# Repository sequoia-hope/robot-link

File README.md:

# robot-link (comms)

### ▶ [Project page: schematic, PCB and 3D viewer](https://sequoia-hope.github.io/robot-link/)

A dev board for ST's 60 GHz contactless link: an **RP2350A** beside an
**ST60A3H1** (antenna in the package), 28 × 63 mm, six layers. Two boards
face each other a few centimetres apart and tunnel UART, GPIO, I²C or
USB 2.0 between them. The same board is either end. On the back there is a
connector for an **OV2640** camera module.

**Status: rev B captured, placed and routed. 100 parts, 83 nets; KiCad's DRC
and ERC report nothing, KiCad's own netlist of the drawn schematic matches
`tools/circuit.py` net for net, every placed part has an LCSC number and
the assembly check passes. Not fabricated, and no firmware yet.**

- **Rev A** (tag `rev-a`): the link board, four layers. Reviewed on
  2026-10-02; what the review found and changed is [below](#review).
- **Rev B**: rev A plus the [camera](#the-camera-rev-b), and six layers.

- `index.html` — status page with the board viewer (SCH, PCB, 3D); published
  from `main` at <https://sequoia-hope.github.io/robot-link/> by GitHub Pages, and
  served locally with `proj up comms`, address from `proj url comms`
- `hardware/comms/` — the KiCad project
- `tools/` — everything is generated; see below

## Why the ST60A3H1 and not the ST60A2G0

The board was asked for with the ST60A2G0. That part's ball map, pin
functions and the 60 GHz antenna and PCB-transition design are only in ST's
NDA package; the public data brief has the package outline and a block
diagram. The ST60A3H1 is the same family with a public data sheet
(DS14598) and the antenna in the package, so there is no 60 GHz copper to
design. It gives up speed: 480 Mbit/s (eUSB2) against the A2's 6.25 Gbit/s
SLVS.

## What is on it

| | |
|---|---|
| MCU | RP2350A with its core regulator, crystal, flash and decoupling as Raspberry Pi's minimal design (RP-006440) has them — the copper round the chip is read out of that board file |
| Link | ST60A3H1 on a grounded island with a copper-free ring round it, 3.5 mm in from the board edge, as on ST's X-NUCLEO-60K1A1 (B2379A) |
| Translator | TXS0108E, 1.8 V ↔ 3.3 V, on the configuration bus, the four tunnel pins, MODE_INT and LINK_STATUS; off until the RP2350 enables it. 4k7 pull-ups on the 1.8 V side of the configuration bus and of the tunnelled SCL/SDA |
| USB | PTN3222 eUSB2 repeater and two TS3USB221A switches: connector, RP2350 and the 60 GHz link, any two joined |
| Power | USB-C 5 V → AMS1117-3.3 → TLV75518P (1.8 V, off until GPIO11 goes high; dropping it is the ST60's power-on reset) |
| I/O | two 1 × 16 headers 0.9 in apart, SWD on JST-SH, BOOTSEL, RUN, power / link / user LEDs |
| Camera | on the back: a 24-way flex connector for the common OV2640 module (the ESP32-CAM's), its 2.8 V and 1.3 V regulators, pull-ups. Its signals are header GPIO |
| Mechanical | four M2.5 holes mirrored about the antenna's axis: a second board turned over on standoffs puts the two antennas on one line. Three fiducials |

GPIO map (`tools/circuit.py` has the reasons): 0–7 right-hand header · 8/9 USB
path selects · 10 RF_EN · 11 1.8 V enable · 12/13 tunnelled SDA/SCL (I2C0) ·
14 LINK_STATUS · 15 MODE_INT · 16/17 tunnelled TXD/RXD (UART0) · 18/19
configuration bus (I2C1; ST60A3H1 at 0x60, PTN3222 at 0x43) · 20 translator
enable · 21–24, 26–29 left-hand header · 25 LED.

## The camera (rev B)

For the bare OV2640 module with a 24-way, 0.5 mm flex tail: the one on the
ESP32-CAM. The connector (Hirose FH12-24S-0.5SH, bottom contact) is on the
**back** of the board. The tail goes in from the USB end with its contacts
toward the board; the module then lies on the back, behind the RP2350, with
its lens looking away from the board. That is the side away from the board
the 60 GHz link faces.

| Camera | GPIO | |
|---|---|---|
| Y2 – Y9 (data) | 0 – 7 | in order: one PIO `in pins, 8` |
| VSYNC | 21 | |
| SIOD / SIOC | 22 / 23 | I2C1, on its second pair of pins (the link's configuration bus is I2C1 on 18/19: move the peripheral, the buses do not share a wire). 4k7 pull-ups |
| PWDN | 24 | 10 k pull-up: the camera sleeps until this is driven low |
| HREF | 26 | |
| XCLK | 27 | from PWM slice 5 B, or PIO: 6 – 24 MHz, so 150 MHz ÷ 8, 10 or 12 (÷ 6 is 25 MHz, too fast). Low drive strength, slow slew: it runs beside PCLK |
| PCLK | 28 | |
| RESET | none | 10 k and 1 µF; the sensor has a software reset (COM7 bit 7), to be used once XCLK is running |

These are header pins, and with no camera plugged in they are nothing else:
26–28 are the ADC pins and have no resistor on them. 22, 23 and 24 keep
their pull-ups.

The sensor's core is on 1.3 V (OmniVision's data sheet from v1.8 on: 1.24 to
1.36 V. The older sheets, and the ESP32-CAM, say 1.2 V), its analogue side
on 2.8 V, its I/O on 3.3 V. The regulators have no enable: a fitted camera
in power-down draws 1 – 2 mA. To wake it: start XCLK, wait 10 ms, drive
PWDN low, reset it over SCCB, then configure.

The order of signals on GPIO 21–28 is not free. The camera's wiring is laid
by hand on the back, from the headers' own through-hole pads to the
connector, in one layer with nothing crossing, and only this order allows
that (`gen_board.camera_copper`).

**Checked, not tested:** which end of the connector is pin 1. The module
makers number the tail one way and the ESP32-CAM's schematic the other. The
board's pads were checked signal by signal, twice and independently, against
two module makers' mechanical drawings and Hirose's data sheet (contacts on
the face away from the lens; with the tail toward you and the contacts up,
NC and AGND on the right, Y0 and Y1 on the left). Check the module in hand
against that before plugging it in: a variant with a mirrored tail would be
the one way this is wrong.

An independent review of the camera addition (2026-10-02) confirmed the pin
order and found four things, all changed: the core supply (was 1.2 V), 100 nF
on each rail at the connector and wider supply tracks, more room round XCLK
where the wiring allows it, and the module's outline on the silkscreen, which
was 2.7 mm out. Left as they are: XCLK still runs 0.125 mm from PCLK and HREF
under the connector (the pads' order puts it between them); DOVDD is 3.3 V,
the data sheet's maximum, as on the ESP32-CAM.

With the headers soldered pins-down straight into a carrier board there is
about 2.5 mm under the board, and the module is 5.5 mm tall: it needs
sockets, or the headers the other way up.

## Board rules

Six layers, JLCPCB's JLC06161H-7628 stack: F.Cu parts and signals, In1 solid
ground, In2 and In3 routed signals, In4 supplies (+3V3, with +1V8 over the
link section), B.Cu signals, the camera's wiring and its parts. The outer
prepreg is the same 0.21 mm as JLCPCB's four-layer stack, so the antenna's
ground and the USB pairs sit as they did on rev A. Routed signals are
0.125 mm track and clearance (JLCPCB's floor is 0.09), and so are the ST60's
ball escapes. The USB pairs on the back are 0.28 mm wide and 0.16 mm apart.
Vias 0.46 / 0.2 mm, all through.

Why six: rev A routed on four. With the camera's wiring and parts on the
back, the same board on four layers left two to seven nets open in each of
three attempts, the nets at the RP2350's pins that had been marginal on
rev A. On six it closes in one or two.

## Ordering and using it

- **JLCPCB Standard PCBA, not Economic**: the ST60A3H1 is a 0.4 mm BGA, and
  Economic stops at 0.5 mm. Standard wants edge rails (JLCPCB adds them) and
  fiducials (three are on the board). Ask for a 0.10 mm stencil.
- Fifteen parts are on the back (the camera's): assembly is two-sided. To
  build the board without the camera, leave the back unassembled; nothing
  on the front depends on it.
- Green solder mask: the ST60's mask openings are 0.30 mm on 0.25 mm lands,
  which leaves 0.10 mm webs between balls, JLCPCB's minimum for green.
- Four vias sit in the gap in the ST60's ball field, tented. Plugged vias
  are the safer order.
- Fit the headers **pins down**, and use **nylon** standoffs at the antenna
  end (H1, H2): metal 11 mm from the patch is inside its beam.
- Firmware: +1V8 is off at reset. Raise GPIO11, wait 2.25 ms, then enable
  the translator (GPIO20) and RF_EN (GPIO10). Before dropping +1V8, take
  both low first. The PTN3222 is held in reset whenever the RF link is down,
  so anything written to it has to be written again after each link-up.
- VBUS on the headers is the USB-C connector's VBUS, direct: it is an
  output. Do not feed 5 V into it with a host plugged in.
- Pull-ups added on J2/J3 (the 3.3 V side of the translator) should be
  8k2 or more.

## The tools

```
python3 tools/circuit.py        # the netlist, as data, and its checks
python3 tools/symbols.py        # hardware/parts/comms.kicad_sym
python3 tools/footprints.py     # hardware/parts/comms.pretty
python3 tools/placement.py      # where every part sits, and its checks
python3 tools/gen_board.py --force   # project, schematic and the unrouted board (DISCARDS routing)
python3 tools/route.py          # freerouting on a stripped copy, results copied back, stitching
python3 tools/schdraw.py --check     # KiCad's netlist of the schematic against circuit.py
python3 tools/assembly.py       # IPC-2581, the pin-1 answers beside it, boardvis's check
python3 tools/regen.py          # every check, then the viewer and the status line on index.html
```

`gen_board.py` lays the copper that is decided rather than routed: Raspberry
Pi's tracks and pours round the RP2350, the ST60's ball field and antenna
ground (ST's own via pattern, hole for hole where it fits), the 480 Mbit/s
USB pair, a via beside every pad on a plane net,
the camera's wiring.
`route.py` hands the remaining ~70 signals to freerouting 2.2.4
(`~/Software/magnet/route`); it is not deterministic, so it makes several
attempts and keeps the first that closes everything.

## Review

Two independent passes on 2026-10-02, one over the schematic against the
data sheets and one over the layout against JLCPCB's limits and ST's
reference board. Neither found anything that would stop the board working.
What they found, and what was done:

| Finding | Done |
|---|---|
| The antenna ground was a quarter of ST's: 13 vias in the island and 15 round it, where B2379A has 53 and 56; the signals crossed the island on a diagonal | The ball field is laid as ST lays it: nine signals straight out through one side of the ring, the supply along the top of them. ST's vias are taken from its drill file: 33 fit in the island and 45 round it |
| +1V8 fall time marginal against the ST60's 1 ms limit (3.3 µF on a 120 Ω discharge) | 1.8 µF on the rail; the regulator's enable is pulled down, so the rail only rises with 3V3 settled |
| MODE_INT strap undefined if +1V8 is cycled with the translator on | 4k7 to ground on MODE_INT |
| No pull-ups on the I²C lines; ST60 and PTN3222 both want external ones | 4k7 to +1V8 on the configuration bus and on GPIO[2]/[3] |
| USB pair geometry computed at 100 Ω; it crossed two plane splits and ran 2.4 mm over no plane | 0.28 / 0.16 mm (89 Ω by the reviewer's field solver); +1V8 plane redrawn so the pair has +3V3 under it throughout; its copper now 0.8 mm from the board edge, not 0.57 |
| Solder-mask webs between balls 0.075 mm | Mask opening 0.30 mm, webs 0.10 mm |
| Silkscreen under JLCPCB's 1.0 mm / 0.15 mm | Back labels 1.0 mm, front 0.8 mm (what fits a 2.54 mm pitch), all lines 0.15 mm |
| VBUS ran under the USB-C shell | Joined on the back |
| LEDs near dark at 1 kΩ (Vf 3.1 V) | 220 Ω |
| No fiducials | Three |
| Four 3V3 capacitors at the RP2350 fed only through the ring under the chip; one via pair into the plane at the regulator | A via beside each of the four capacitors; five more at the regulator's tab |

Left as it is, knowingly:

- **TXS0108E on the I²C lines.** The reviewer would rather have a pass-FET
  translator with no edge accelerators there: the ST60 has no glitch filter
  on CFG_SCL. ST's own board uses an auto-direction part (ST2378E) on the
  same lines; that part's data sheet was not read. If the configuration bus
  misbehaves with wiring on J2, this is the first place to look.
- **AMS1117 with ceramic output capacitors**, as Raspberry Pi's reference has
  an 1117: outside what the AMS data sheet characterises (22 µF tantalum).
  It needs about 1 V of headroom, so VBUS has to stay above 4.35 V.
- **The crystal** is servodrive's 2520 (CL 20 pF) with 27 pF, where Raspberry
  Pi specifies an ABM8-272 with 15 pF and says any change needs testing.
- **USB pair skew**: D− is 1.1 mm longer than D+ between the connector and
  the first switch (its two pads are joined under the shell). The long run
  to the repeater is matched to 0.05 mm.
- **The ground guard round the crystal** in the reference was not copied;
  three signals pass within 0.13 mm of the crystal nets.

## Not yet verified

- Nothing has been built. The ST60A3H1 land and the PTN3222 land are drawn
  from the manufacturers' drawings, not from a part in hand.
- The antenna island copies ST's dimensions and vias off their Gerbers; the
  pattern on this board has not been simulated or measured, and it has
  fewer vias than ST's where this board's tracks are in the way.
- The 89 Ω figure for the USB pairs is one reviewer's solver, checked
  against a textbook formula only. Confirm with JLCPCB's calculator.
- JLCPCB capability figures were read off their site on 2026-10-02 through
  a summarising tool, not from the raw pages. Check them at order time.
- Several pin-1 answers in the assembly sidecar are package convention,
  not read off that part's data sheet; the sidecar says which.
- Rev B's camera connector: see "Checked, not tested" above. The camera's
  wiring runs 15 to 40 mm on the back over the supply plane; nothing about
  its signal integrity at a 20 MHz pixel clock has been measured.
- The 2.8 V regulator is listed as UMW's XC6206; its data sheet numbers the
  pins oddly, and the reviewer read it as the same physical order as Torex's.

## Next

Firmware: the link's bring-up sequence, a PIO capture for the camera. Then
a first build.

CERN-OHL-P.

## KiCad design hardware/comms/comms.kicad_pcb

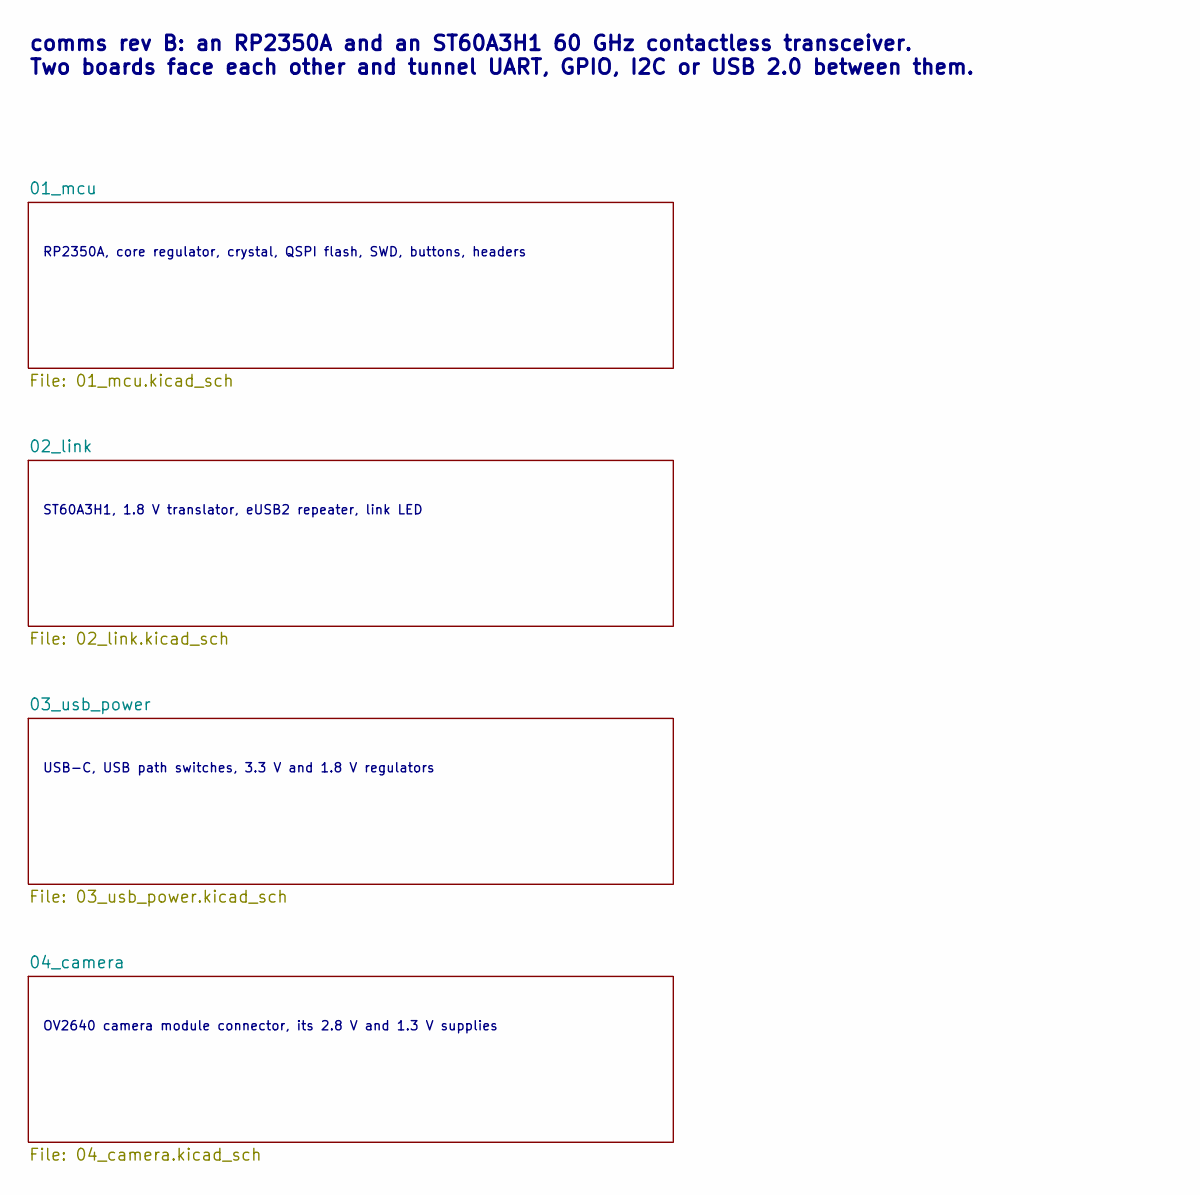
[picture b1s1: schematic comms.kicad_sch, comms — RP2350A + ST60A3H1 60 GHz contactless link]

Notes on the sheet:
RP2350A, core regulator, crystal, QSPI flash, SWD, buttons, headers
ST60A3H1, 1.8 V translator, eUSB2 repeater, link LED
USB-C, USB path switches, 3.3 V and 1.8 V regulators
OV2640 camera module connector, its 2.8 V and 1.3 V supplies
comms rev B: an RP2350A and an ST60A3H1 60 GHz contactless transceiver. Two boards face each other and tunnel UART, GPIO, I2C or USB 2.0 between them.

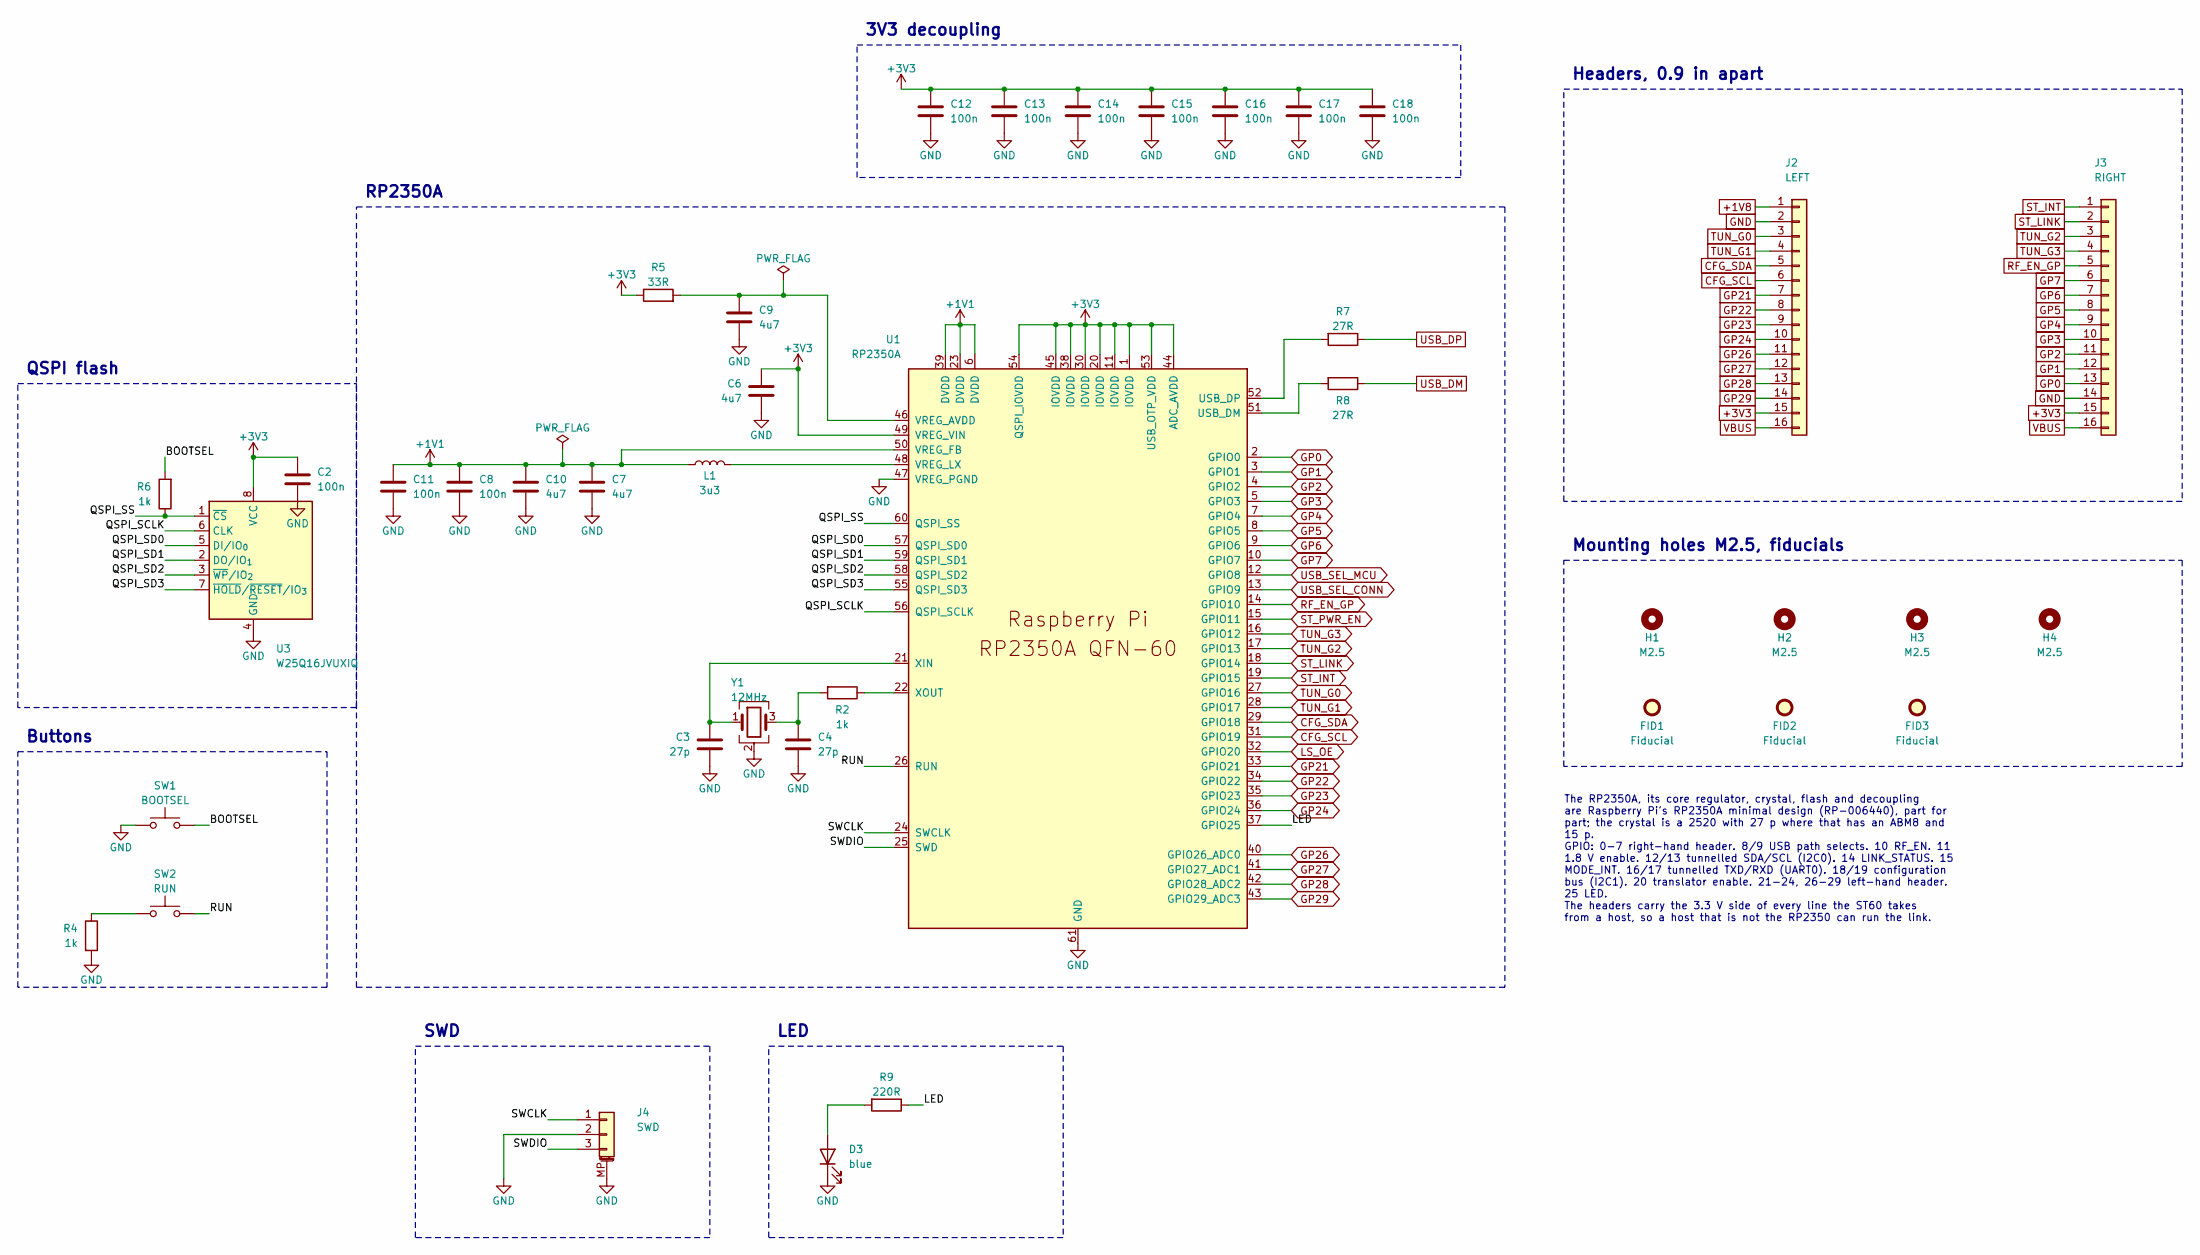
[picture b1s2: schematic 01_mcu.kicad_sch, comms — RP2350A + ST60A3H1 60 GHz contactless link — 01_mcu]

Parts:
C2, C8, C11, C12, C13, C14, C15, C16, C17, C18: 100n; C_0402_1005Metric
C3, C4: 27p; C_0402_1005Metric
C6, C7: 4u7; C_0402_1005Metric_small_pads
C9, C10: 4u7; C_0402_1005Metric
D3: blue; LED_0603_1608Metric
FID1, FID2, FID3: Fiducial; Fiducial_1mm_Mask2mm
H1, H2, H3, H4: M2.5; MountingHole_2.7mm_M2.5
J2: LEFT; PinHeader_1x16_P2.54mm_Vertical
J3: RIGHT; PinHeader_1x16_P2.54mm_Vertical
J4: SWD; JST_SH_SM03B-SRSS-TB_1x03-1MP_P1.00mm_Horizontal
L1: 3u3; L_pol_2016
R2, R4, R6: 1k; R_0402_1005Metric
R5: 33R; R_0402_1005Metric
R7, R8: 27R; R_0402_1005Metric
R9: 220R; R_0402_1005Metric
SW1: BOOTSEL; SW_SPST_B3U-1000P
SW2: RUN; SW_SPST_B3U-1000P
U1: RP2350A; RP2350-QFN-60-1EP_7x7_P0.4mm_EP3.4x3.4mm_ThermalVias
U3: W25Q16JVUXIQ; Winbond_USON-8-1EP_3x2mm_P0.5mm_EP0.2x1.6mm
Y1: 12MHz; Crystal_SMD_2520-4Pin_2.5x2.0mm

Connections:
+1V1: C7.1, C8.1, C10.1, C11.1, L1.1, U1.6 (DVDD), U1.23 (DVDD), U1.39 (DVDD), U1.50 (VREG_FB)
+1V8: J2.1; also elsewhere on the board
+3V3: C2.1, C6.1, C12.1, C13.1, C14.1, C15.1, C16.1, C17.1, C18.1, J2.15, J3.15, R5.1, U1.1 (IOVDD), U1.11 (IOVDD), U1.20 (IOVDD), U1.30 (IOVDD), U1.38 (IOVDD), U1.44 (ADC_AVDD), U1.45 (IOVDD), U1.49 (VREG_VIN), U1.53 (USB_OTP_VDD), U1.54 (QSPI_IOVDD), U3.8 (VCC); also elsewhere on the board
BOOTSEL: R6.2, SW1.2
CFG_SCL: J2.6, U1.31 (GPIO19); also elsewhere on the board
CFG_SDA: J2.5, U1.29 (GPIO18); also elsewhere on the board
GND: C2.2, C3.2, C4.2, C6.2, C7.2, C8.2, C9.2, C10.2, C11.2, C12.2, C13.2, C14.2, C15.2, C16.2, C17.2, C18.2, D3.1 (K), J2.2, J3.14, J4.2, J4.MP (MountPin), R4.2, SW1.1, U1.47 (VREG_PGND), U1.61 (GND), U3.4 (GND), Y1.2 (G), Y1.4 (G); also elsewhere on the board
GP0: J3.13, U1.2 (GPIO0); also elsewhere on the board
GP1: J3.12, U1.3 (GPIO1); also elsewhere on the board
GP2: J3.11, U1.4 (GPIO2); also elsewhere on the board
GP3: J3.10, U1.5 (GPIO3); also elsewhere on the board
GP4: J3.9, U1.7 (GPIO4); also elsewhere on the board
GP5: J3.8, U1.8 (GPIO5); also elsewhere on the board
GP6: J3.7, U1.9 (GPIO6); also elsewhere on the board
GP7: J3.6, U1.10 (GPIO7); also elsewhere on the board
GP21: J2.7, U1.33 (GPIO21); also elsewhere on the board
GP22: J2.8, U1.34 (GPIO22); also elsewhere on the board
GP23: J2.9, U1.35 (GPIO23); also elsewhere on the board
GP24: J2.10, U1.36 (GPIO24); also elsewhere on the board
GP26: J2.11, U1.40 (GPIO26_ADC0); also elsewhere on the board
GP27: J2.12, U1.41 (GPIO27_ADC1); also elsewhere on the board
GP28: J2.13, U1.42 (GPIO28_ADC2); also elsewhere on the board
GP29: J2.14, U1.43 (GPIO29_ADC3)
LED: R9.1, U1.37 (GPIO25)
LED_A: D3.2 (A), R9.2
LS_OE: U1.32 (GPIO20); also elsewhere on the board
QSPI_SCLK: U1.56 (QSPI_SCLK), U3.6 (CLK)
QSPI_SD0: U1.57 (QSPI_SD0), U3.5 (DI/IO_{0})
QSPI_SD1: U1.59 (QSPI_SD1), U3.2 (DO/IO_{1})
QSPI_SD2: U1.58 (QSPI_SD2), U3.3 (~WP/IO_{2})
QSPI_SD3: U1.55 (QSPI_SD3), U3.7 (~HOLD/~RESET/IO_{3})
QSPI_SS: R6.1, U1.60 (QSPI_SS), U3.1 (~CS)
RF_EN_GP: J3.5, U1.14 (GPIO10); also elsewhere on the board
RUN: SW2.2, U1.26 (RUN)
RUN_SW: R4.1, SW2.1
ST_INT: J3.1, U1.19 (GPIO15); also elsewhere on the board
ST_LINK: J3.2, U1.18 (GPIO14); also elsewhere on the board
ST_PWR_EN: U1.15 (GPIO11); also elsewhere on the board
SWCLK: J4.1, U1.24 (SWCLK)
SWDIO: J4.3, U1.25 (SWD)
TUN_G0: J2.3, U1.27 (GPIO16); also elsewhere on the board
TUN_G1: J2.4, U1.28 (GPIO17); also elsewhere on the board
TUN_G2: J3.3, U1.17 (GPIO13); also elsewhere on the board
TUN_G3: J3.4, U1.16 (GPIO12); also elsewhere on the board
USB_DM: R8.1; also elsewhere on the board
USB_DM_C: R8.2, U1.51 (USB_DM)
USB_DP: R7.1; also elsewhere on the board
USB_DP_C: R7.2, U1.52 (USB_DP)
USB_SEL_CONN: U1.13 (GPIO9); also elsewhere on the board
USB_SEL_MCU: U1.12 (GPIO8); also elsewhere on the board
VBUS: J2.16, J3.16; also elsewhere on the board
VREG_AVDD: C9.1, R5.2, U1.46 (VREG_AVDD)
VREG_LX: L1.2, U1.48 (VREG_LX)
XIN: C3.1, U1.21 (XIN), Y1.1
XOUT: R2.1, U1.22 (XOUT)
XTAL2: C4.1, R2.2, Y1.3

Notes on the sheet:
RP2350A
3V3 decoupling
QSPI flash
Buttons
SWD
LED
Headers, 0.9 in apart
Mounting holes M2.5, fiducials
The RP2350A, its core regulator, crystal, flash and decoupling are Raspberry Pi's RP2350A minimal design (RP-006440), part for part; the crystal is a 2520 with 27 p where that has an ABM8 and 15 p. GPIO: 0-7 right-hand header. 8/9 USB path selects. 10 RF_EN. 11 1.8 V enable. 12/13 tunnelled SDA/SCL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

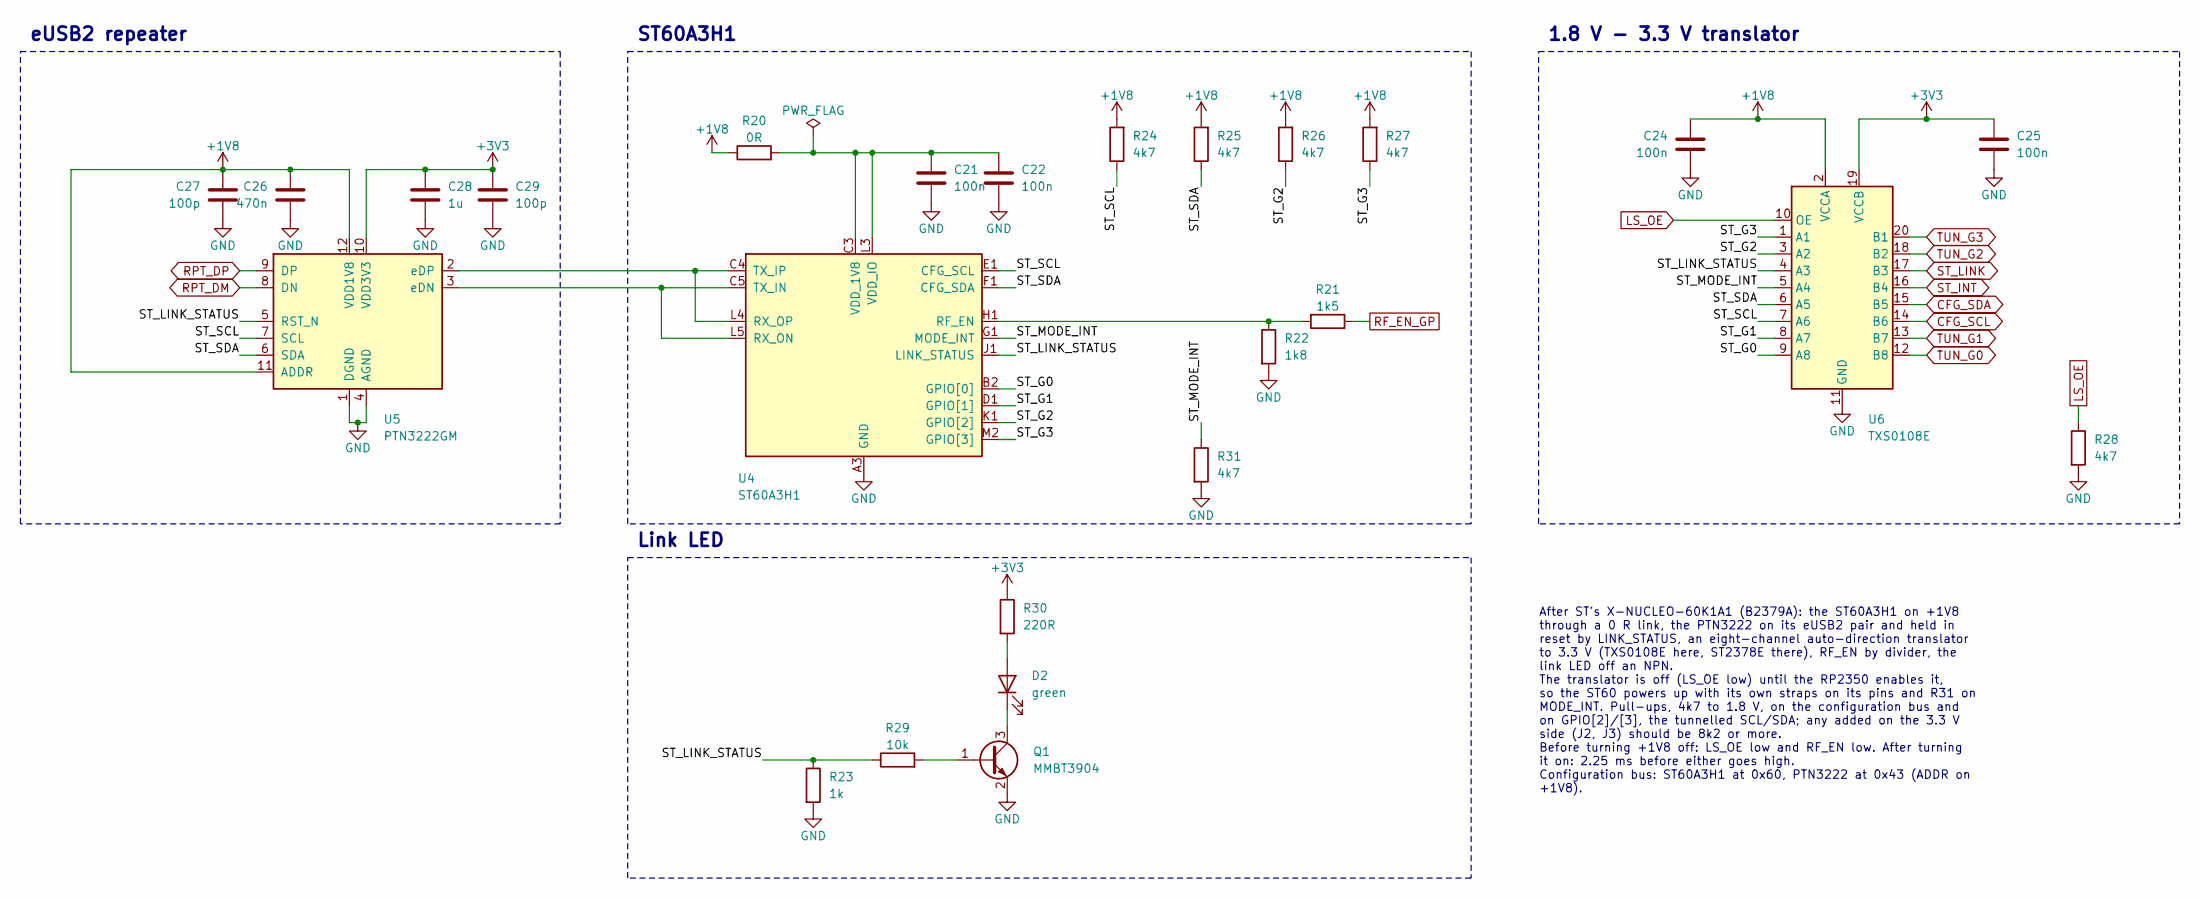
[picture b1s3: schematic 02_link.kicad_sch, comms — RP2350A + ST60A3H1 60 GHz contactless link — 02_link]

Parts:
C21, C22, C24, C25: 100n; C_0402_1005Metric
C26: 470n; C_0402_1005Metric
C27, C29: 100p; C_0402_1005Metric
C28: 1u; C_0402_1005Metric
D2: green; LED_0603_1608Metric
Q1: MMBT3904; SOT-23
R20: 0R; R_0402_1005Metric
R21: 1k5; R_0402_1005Metric
R22: 1k8; R_0402_1005Metric
R23: 1k; R_0402_1005Metric
R24, R25, R26, R27, R28, R31: 4k7; R_0402_1005Metric
R29: 10k; R_0402_1005Metric
R30: 220R; R_0402_1005Metric
U4: ST60A3H1; ST_VFBGA-23_AiP_2.95x4.07mm_P0.4mm
U5: PTN3222GM; NXP_XQFN-12_1.75x2.2mm_P0.4mm
U6: TXS0108E; TSSOP-20_4.4x6.5mm_P0.65mm

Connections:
+1V8: C24.1, C26.1, C27.1, R20.1, R24.2, R25.2, R26.2, R27.2, U5.11 (ADDR), U5.12 (VDD1V8), U6.2 (VCCA); also elsewhere on the board
+3V3: C25.1, C28.1, C29.1, R30.1, U5.10 (VDD3V3), U6.19 (VCCB); also elsewhere on the board
CFG_SCL: U6.14 (B6); also elsewhere on the board
CFG_SDA: U6.15 (B5); also elsewhere on the board
EUSB_N: U4.C5 (TX_IN), U4.L5 (RX_ON), U5.3 (eDN)
EUSB_P: U4.C4 (TX_IP), U4.L4 (RX_OP), U5.2 (eDP)
GND: C21.2, C22.2, C24.2, C25.2, C26.2, C27.2, C28.2, C29.2, Q1.2 (E), R22.2, R23.2, R28.2, R31.2, U4.A3 (GND), U4.A4 (GND), U4.A5 (GND), U4.C6 (GND), U4.L6 (GND), U4.N3 (GND), U4.N4 (GND), U4.N5 (GND), U5.1 (DGND), U5.4 (AGND), U6.11 (GND); also elsewhere on the board
LINK_A: D2.2 (A), R30.2
LINK_B: Q1.1 (B), R29.2
LINK_K: D2.1 (K), Q1.3 (C)
LS_OE: R28.1, U6.10 (OE); also elsewhere on the board
RF_EN_GP: R21.1; also elsewhere on the board
RPT_DM: U5.8 (DN); also elsewhere on the board
RPT_DP: U5.9 (DP); also elsewhere on the board
ST_G0: U4.B2 (GPIO[0]), U6.9 (A8)
ST_G1: U4.D1 (GPIO[1]), U6.8 (A7)
ST_G2: R26.1, U4.K1 (GPIO[2]), U6.3 (A2)
ST_G3: R27.1, U4.M2 (GPIO[3]), U6.1 (A1)
ST_INT: U6.16 (B4); also elsewhere on the board
ST_LINK: U6.17 (B3); also elsewhere on the board
ST_LINK_STATUS: R23.1, R29.1, U4.J1 (LINK_STATUS), U5.5 (RST_N), U6.4 (A3)
ST_MODE_INT: R31.1, U4.G1 (MODE_INT), U6.5 (A4)
ST_RF_EN: R21.2, R22.1, U4.H1 (RF_EN)
ST_SCL: R24.1, U4.E1 (CFG_SCL), U5.7 (SCL), U6.7 (A6)
ST_SDA: R25.1, U4.F1 (CFG_SDA), U5.6 (SDA), U6.6 (A5)
ST_VDD: C21.1, C22.1, R20.2, U4.C3 (VDD_1V8), U4.L3 (VDD_IO)
TUN_G0: U6.12 (B8); also elsewhere on the board
TUN_G1: U6.13 (B7); also elsewhere on the board
TUN_G2: U6.18 (B2); also elsewhere on the board
TUN_G3: U6.20 (B1); also elsewhere on the board

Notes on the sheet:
eUSB2 repeater
ST60A3H1
1.8 V - 3.3 V translator
Link LED
After ST's X-NUCLEO-60K1A1 (B2379A): the ST60A3H1 on +1V8 through a 0 R link, the PTN3222 on its eUSB2 pair and held in reset by LINK_STATUS, an eight-channel auto-direction translator to 3.3 V (TXS0108E here, ST2378E there), RF_EN by divider, the link LED off an NPN. The translator is off (LS_OE l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

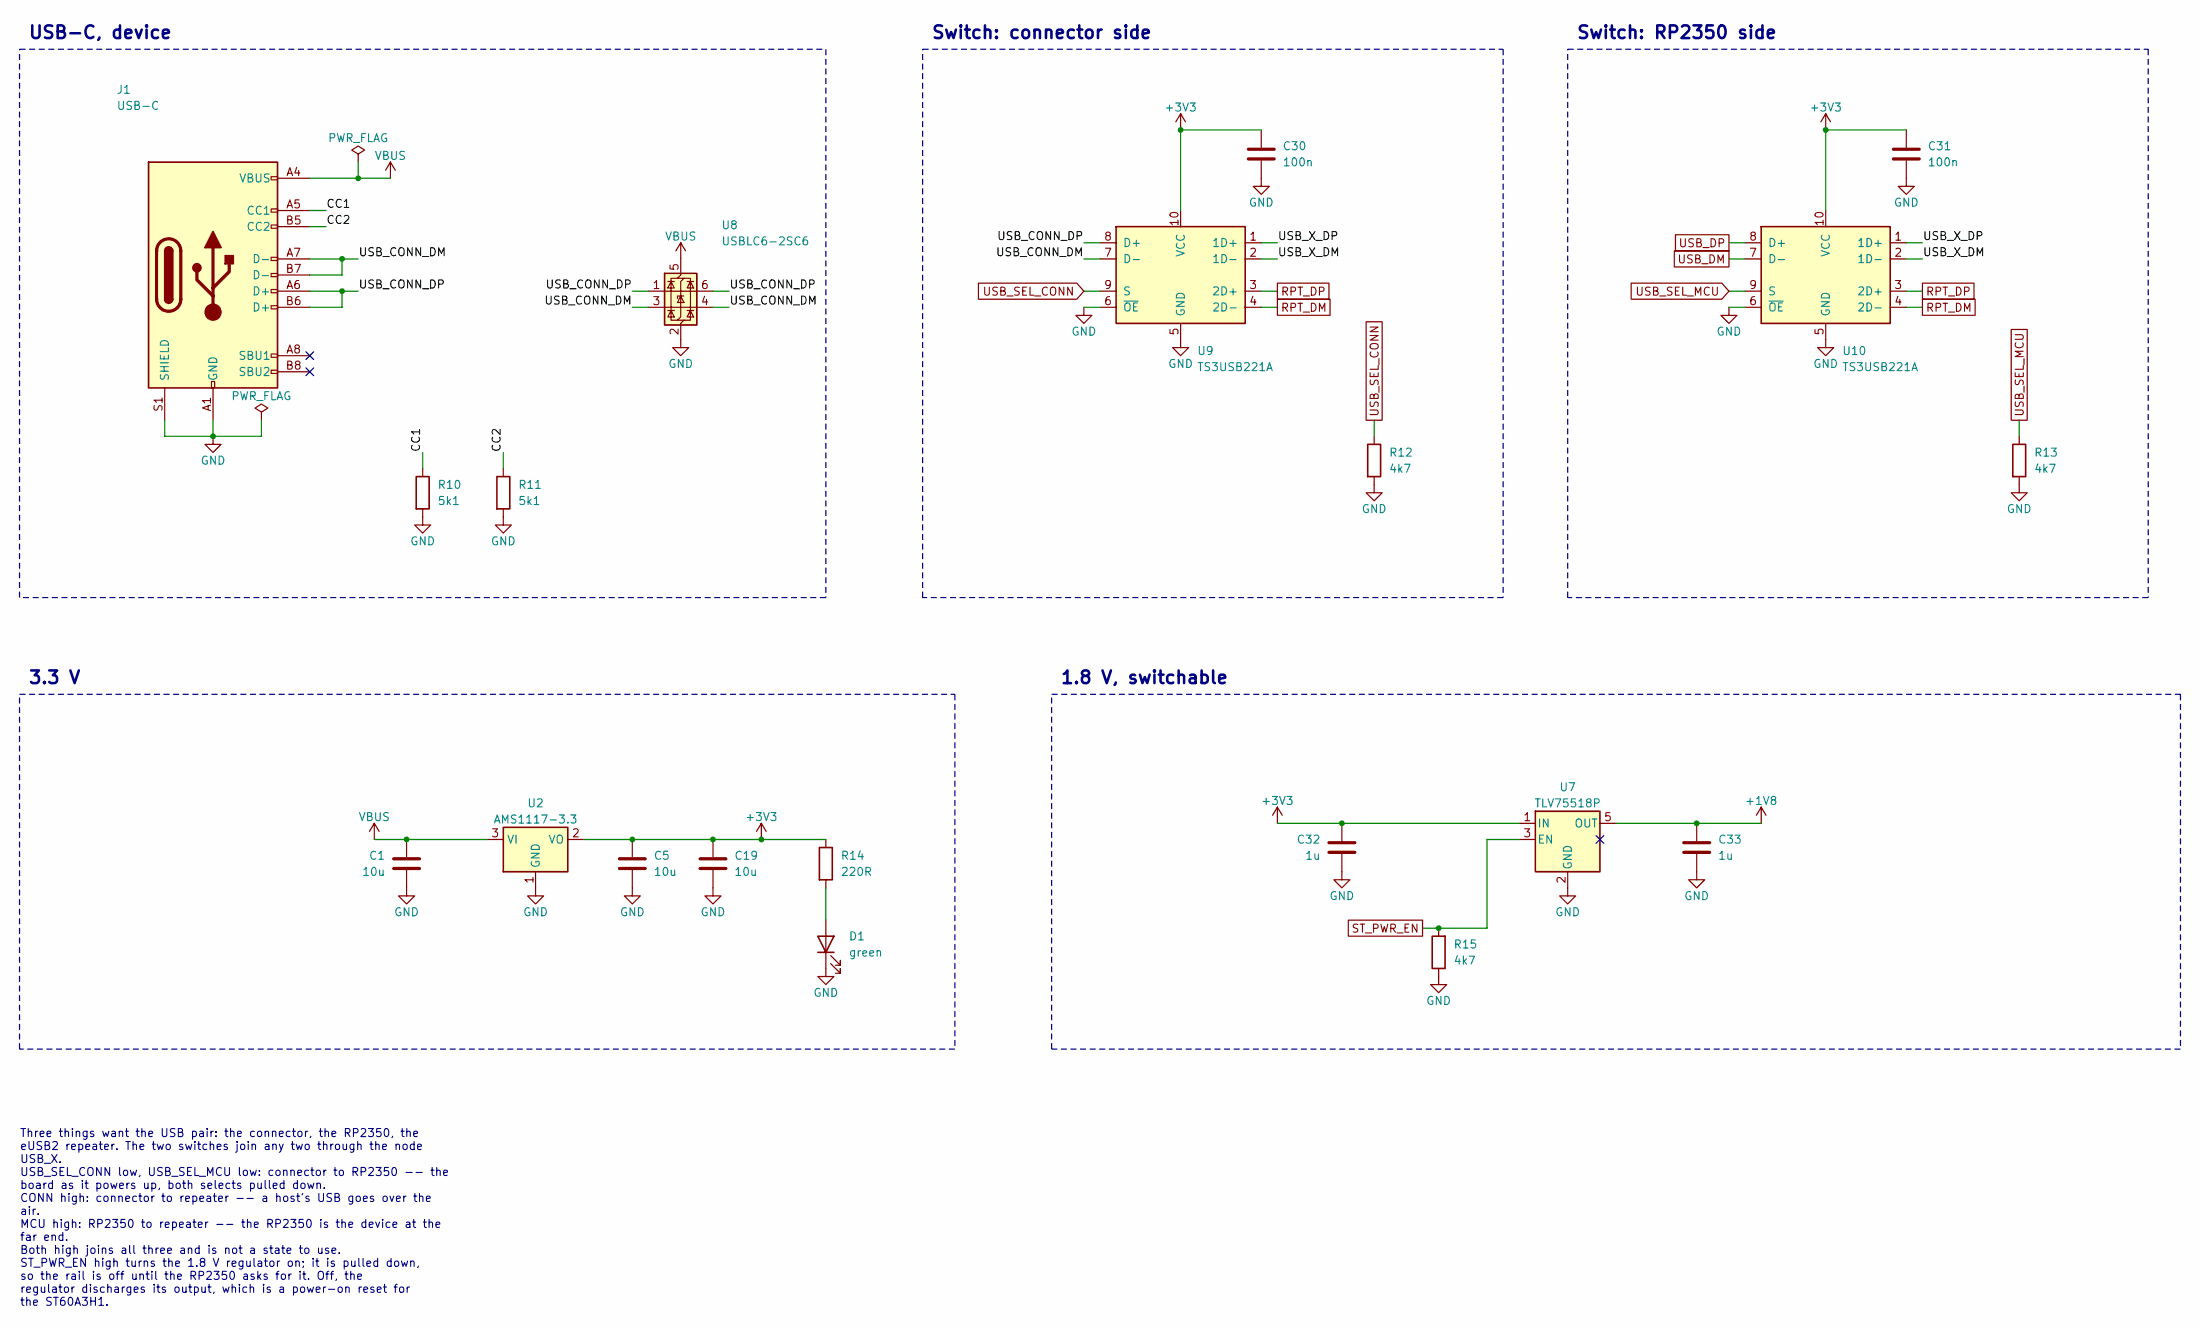
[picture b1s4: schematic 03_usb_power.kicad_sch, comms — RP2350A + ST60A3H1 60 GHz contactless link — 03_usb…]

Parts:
C1, C5, C19: 10u; C_0805_2012Metric
C30, C31: 100n; C_0402_1005Metric
C32, C33: 1u; C_0402_1005Metric
D1: green; LED_0603_1608Metric
J1: USB-C; USB_C_Receptacle_HRO_TYPE-C-31-M-12
R10, R11: 5k1; R_0402_1005Metric
R12, R13, R15: 4k7; R_0402_1005Metric
R14: 220R; R_0402_1005Metric
U2: AMS1117-3.3; SOT-223-3_TabPin2
U7: TLV75518P; SOT-23-5
U8: USBLC6-2SC6; SOT-23-6
U9, U10: TS3USB221A; Texas_UQFN-10_1.5x2mm_P0.5mm

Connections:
+1V8: C33.1, U7.5 (OUT); also elsewhere on the board
+3V3: C5.1, C19.1, C30.1, C31.1, C32.1, R14.1, U2.2 (VO), U7.1 (IN), U9.10 (VCC), U10.10 (VCC); also elsewhere on the board
CC1: J1.A5 (CC1), R10.1
CC2: J1.B5 (CC2), R11.1
GND: C1.2, C5.2, C19.2, C30.2, C31.2, C32.2, C33.2, D1.1 (K), J1.A1 (GND), J1.A12 (GND), J1.B1 (GND), J1.B12 (GND), J1.S1 (SHIELD), R10.2, R11.2, R12.2, R13.2, R15.1, U2.1 (GND), U7.2 (GND), U8.2 (GND), U9.5 (GND), U9.6 (~OE), U10.5 (GND), U10.6 (~OE); also elsewhere on the board
PWR_A: D1.2 (A), R14.2
RPT_DM: U9.4 (2D-), U10.4 (2D-); also elsewhere on the board
RPT_DP: U9.3 (2D+), U10.3 (2D+); also elsewhere on the board
ST_PWR_EN: R15.2, U7.3 (EN); also elsewhere on the board
USB_CONN_DM: J1.A7 (D-), J1.B7 (D-), U8.3 (I/O2), U8.4 (I/O2), U9.7 (D-)
USB_CONN_DP: J1.A6 (D+), J1.B6 (D+), U8.1 (I/O1), U8.6 (I/O1), U9.8 (D+)
USB_DM: U10.7 (D-); also elsewhere on the board
USB_DP: U10.8 (D+); also elsewhere on the board
USB_SEL_CONN: R12.1, U9.9 (S); also elsewhere on the board
USB_SEL_MCU: R13.1, U10.9 (S); also elsewhere on the board
USB_X_DM: U9.2 (1D-), U10.2 (1D-)
USB_X_DP: U9.1 (1D+), U10.1 (1D+)
VBUS: C1.1, J1.A4 (VBUS), J1.A9 (VBUS), J1.B4 (VBUS), J1.B9 (VBUS), U2.3 (VI), U8.5 (VBUS); also elsewhere on the board

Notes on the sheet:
USB-C, device
Switch: connector side
Switch: RP2350 side
3.3 V
1.8 V, switchable
Three things want the USB pair: the connector, the RP2350, the eUSB2 repeater. The two switches join any two through the node USB_X. USB_SEL_CONN low, USB_SEL_MCU low: connector to RP2350 -- the board as it powers up, both selects pulled down. CONN high: connector to repeater -- a host's USB goes o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

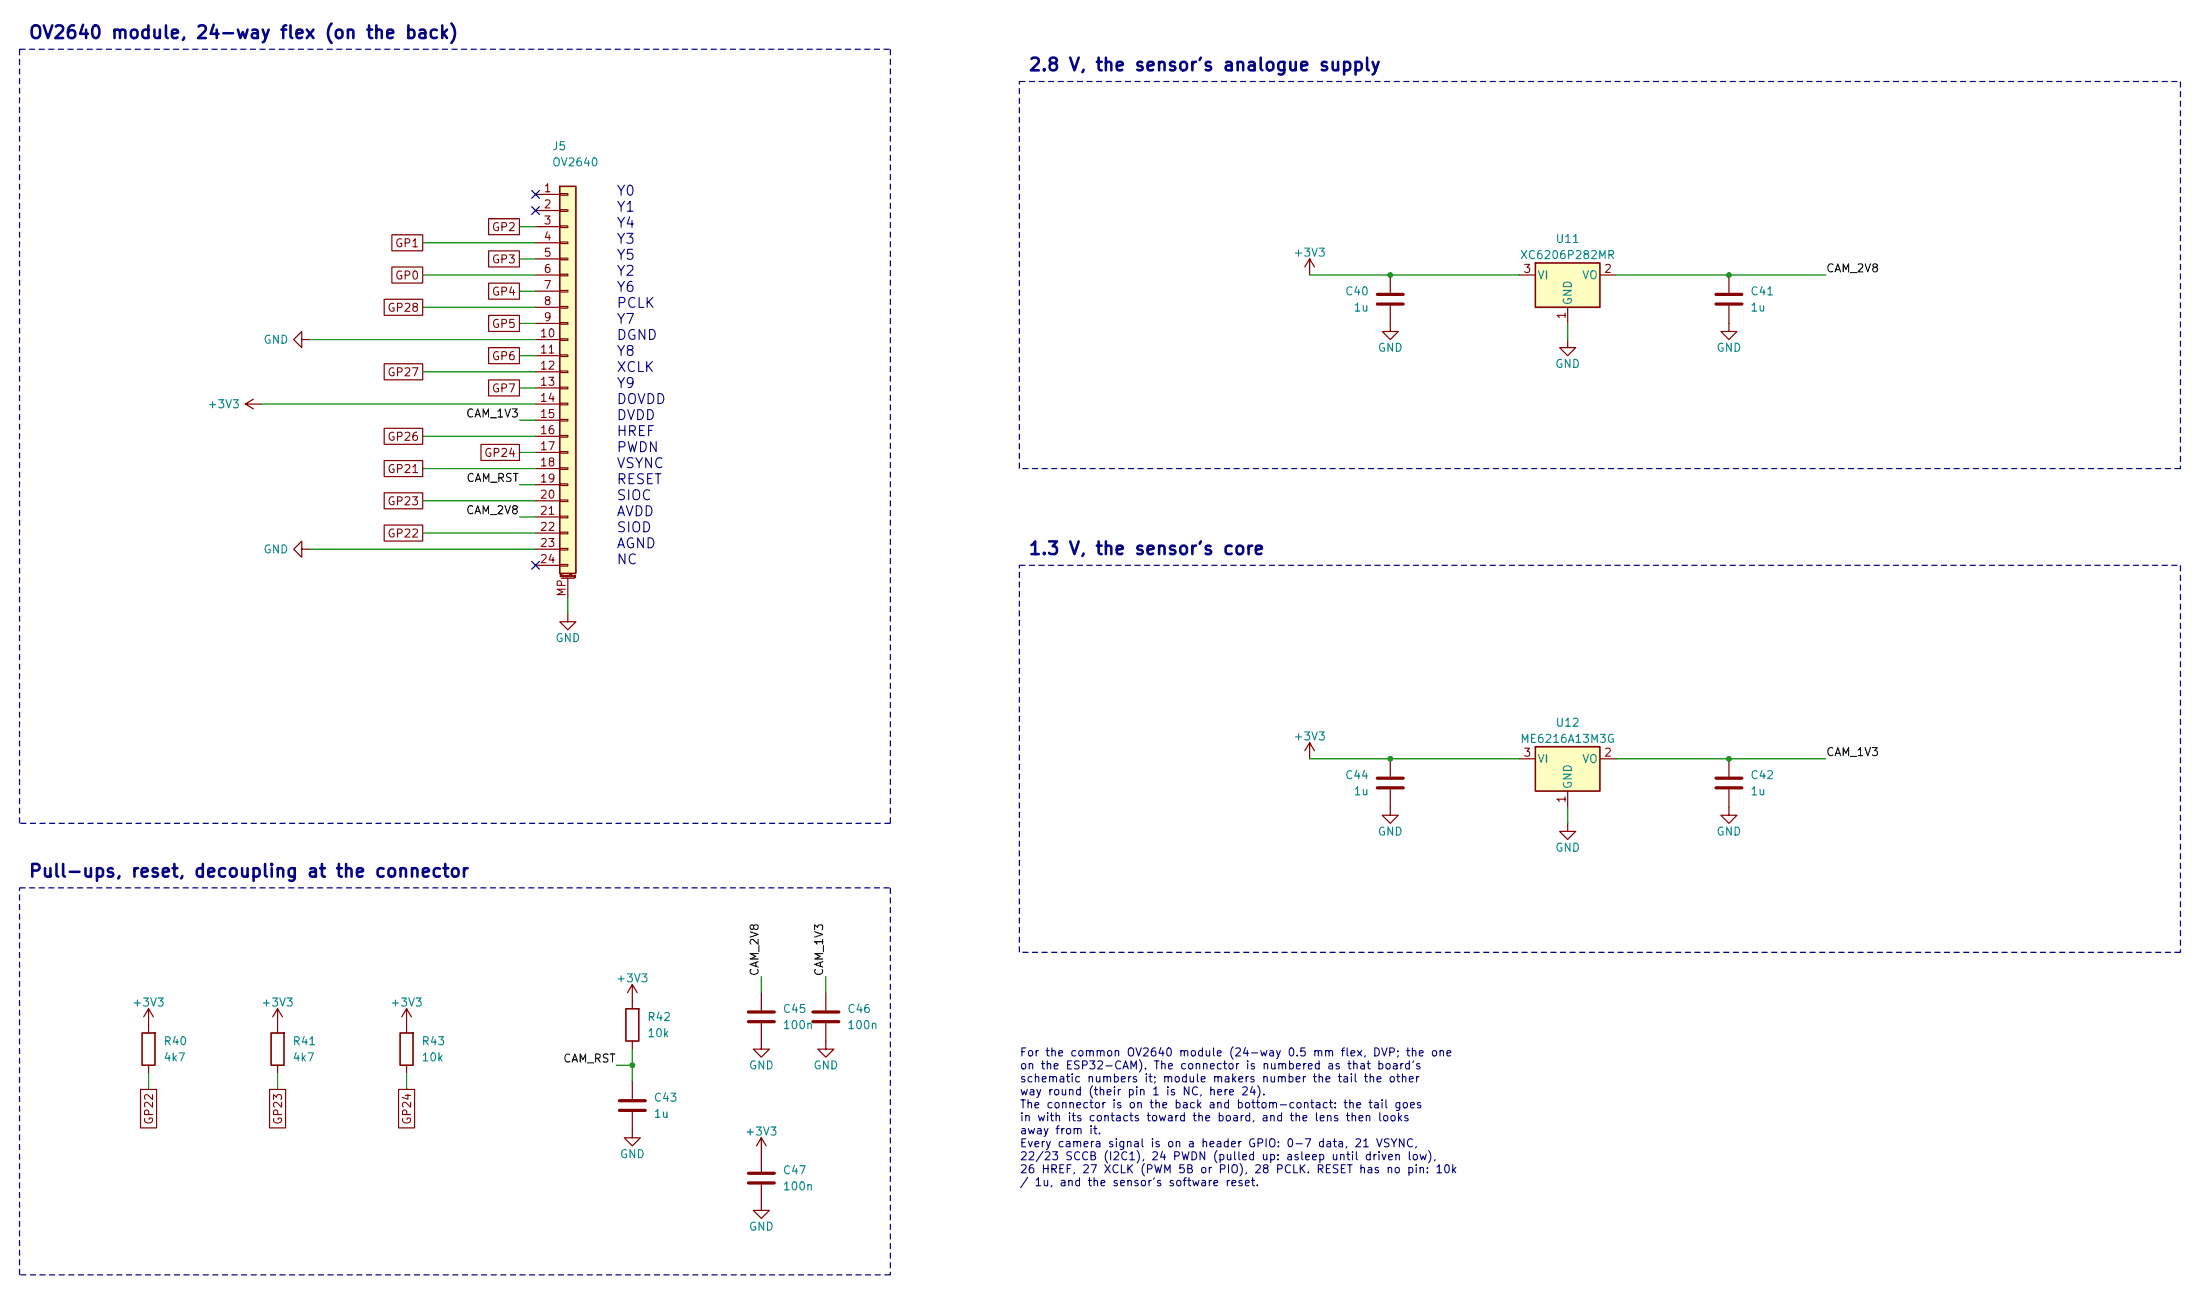
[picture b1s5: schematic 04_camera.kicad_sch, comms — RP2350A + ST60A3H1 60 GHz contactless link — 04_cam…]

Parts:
C40, C41, C42, C43, C44: 1u; C_0402_1005Metric
C45, C46, C47: 100n; C_0402_1005Metric
J5: OV2640; Hirose_FH12-24S-0.5SH_1x24-1MP_P0.50mm_Horizontal
R40, R41: 4k7; R_0402_1005Metric
R42, R43: 10k; R_0402_1005Metric
U11: XC6206P282MR; SOT-23
U12: ME6216A13M3G; SOT-23

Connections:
+3V3: C40.1, C44.1, C47.1, J5.14, R40.2, R41.2, R42.2, R43.2, U11.3 (VI), U12.3 (VI); also elsewhere on the board
CAM_1V3: C42.1, C46.1, J5.15, U12.2 (VO)
CAM_2V8: C41.1, C45.1, J5.21, U11.2 (VO)
CAM_RST: C43.1, J5.19, R42.1
GND: C40.2, C41.2, C42.2, C43.2, C44.2, C45.2, C46.2, C47.2, J5.10, J5.23, J5.MP (MountPin), U11.1 (GND), U12.1 (GND); also elsewhere on the board
GP0: J5.6; also elsewhere on the board
GP1: J5.4; also elsewhere on the board
GP2: J5.3; also elsewhere on the board
GP3: J5.5; also elsewhere on the board
GP4: J5.7; also elsewhere on the board
GP5: J5.9; also elsewhere on the board
GP6: J5.11; also elsewhere on the board
GP7: J5.13; also elsewhere on the board
GP21: J5.18; also elsewhere on the board
GP22: J5.22, R40.1; also elsewhere on the board
GP23: J5.20, R41.1; also elsewhere on the board
GP24: J5.17, R43.1; also elsewhere on the board
GP26: J5.16; also elsewhere on the board
GP27: J5.12; also elsewhere on the board
GP28: J5.8; also elsewhere on the board

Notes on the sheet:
OV2640 module, 24-way flex (on the back)
Pull-ups, reset, decoupling at the connector
2.8 V, the sensor's analogue supply
1.3 V, the sensor's core
Y0 Y1 Y4 Y3 Y5 Y2 Y6 PCLK Y7 DGND Y8 XCLK Y9 DOVDD DVDD HREF PWDN VSYNC RESET SIOC AVDD SIOD AGND NC
For the common OV2640 module (24-way 0.5 mm flex, DVP; the one on the ESP32-CAM). The connector is numbered as that board's schematic numbers it; module makers number the tail the other way round (their pin 1 is NC, here 24). The connector is on the back and bottom-contact: the tail goes in with it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
